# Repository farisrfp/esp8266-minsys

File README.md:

# **ESP8266 Minimum System**

_Workshop Telematika 2023_

## **Deskripsi**

Dokumentasi ini dibuat untuk memudahkan peserta workshop dalam memahami dan mengembangkan ESP8266 Minimum System pada Workshop Telematika 2023.

Diagram Fitur ESP8266 Minimum System dan PCB dapat dilihat pada gambar berikut.

## Hardware

Gambar dibawah merupakan design hardware ESP8266 Minimum System yang akan digunakan pada workshop.

<table>
                <tr>
                    <th>Jalur PCB</th>
                    <th>Hasil Gerber</th>
                    <th>Gambar 3D</th>
                </tr>
                <tr>
                    <td></td>
                    <td></td>
                    <td></td>
                </tr>
</table>

Untuk dokumentasi hardware, silahkan lihat [/hardware](hardware/readme.md)

## Firmware

Untuk dokumentasi firmware, silahkan lihat [/firmware](firmware/readme.md)

## Kontribusi

Kami sangat terbuka terhadap kontribusi dari semua pihak. Jika Anda ingin berkontribusi dengan memperbaiki atau melengkapi template ini, silakan buat pull request ke repositori template kami.

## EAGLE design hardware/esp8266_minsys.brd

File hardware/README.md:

# **Dokumentasi Hardware**

## Software

- [Eagle](https://www.autodesk.com/products/eagle/overview) (Untuk membuka file .sch dan .brd)
- [Fusion 360](https://www.autodesk.com/products/fusion-360/overview) (Alternatif)

## Schematic

Gambar dibawah merupakan schematic ESP8266 Minimum System yang akan digunakan pada workshop.

## Bill of Material

| Designator | Quantity | Package | Value |      Description      |
| :--------: | :------: | :-----: | :---: | :-------------------: |
|  R1 - R4   |    4     |  0805   |  10K  |       Resistor        |
|  R5 - R7   |    3     |  0805   |  330  |       Resistor        |
|  R8 - R10  |    3     |  0805   |  100  |       Resistor        |
|    R11     |    1     |  0805   |  1K   |       Resistor        |
|     C1     |    1     |  2412   | 100u  |       Kapasitor       |
|  C2 - C3   |    2     |  0805   |  10u  |       Kapasitor       |
|     D1     |    1     |  5050   |  RGB  |          LED          |
|     D2     |    1     |  0805   |  Red  |          LED          |
|    SW1     |    1     |    -    |   -   |    Push Button (1)    |
| SW2 - SW3  |    1     |    -    |   -   |    Push Button (2)    |
|    IC1     |    1     | SOT-223 |  3V3  | Voltage Regulator 3V3 |
|     F1     |    1     |  1206   | 750mA |         Fuse          |
|     J1     |    1     |    -    |  6P   |      USB Type-C       |

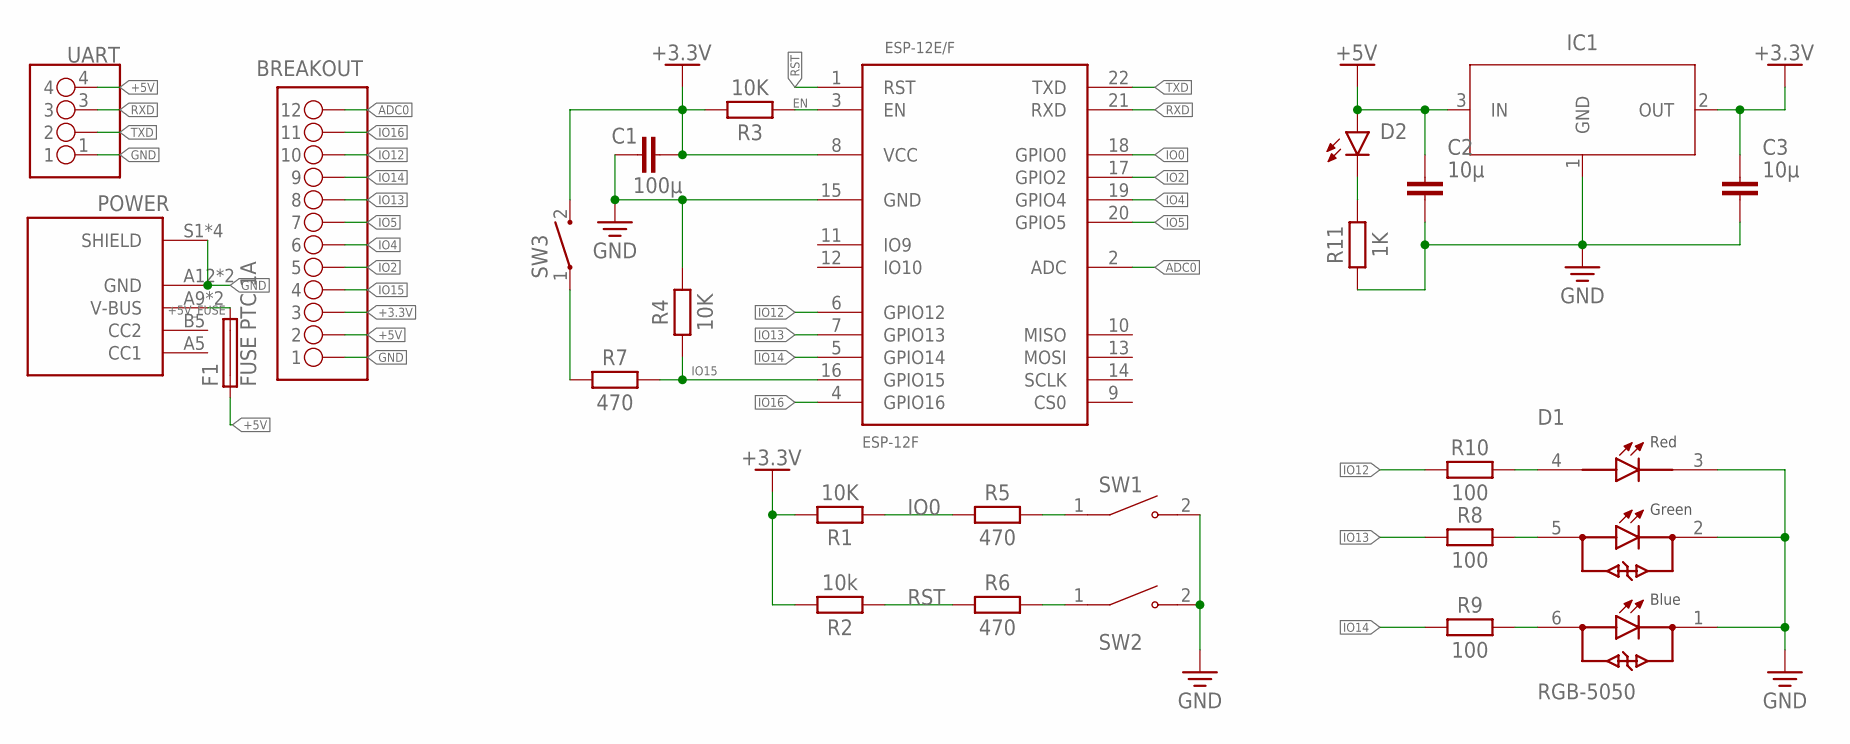
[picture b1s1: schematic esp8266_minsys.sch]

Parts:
BREAKOUT: PINHD-1X12-BACKUP_1X12M; 1X12
C1: 100µ; CAPM6032X280
C2, C3: 10µ; CAPC2012X110
D1: RGB-5050
D2: LED_RED; LEDC2012X110N_FLAT-R
ESP-12E/F: ESP-12F
F1: FUSE PTC 1A; FUSC3215X82N
IC1: NCP1117ST33T3G; SOT230P700X170-4
POWER: SOCKET-C
R1, R3, R4: 10K; RESC2012X65
R2: 10k; RESC2012X65
R5, R6, R7: 470; RESC2012X65
R8, R9, R10: 100; RESC2012X65
R11: 1K; RESC2012X65
SW1, SW2: SWITCH-2P
SW3: SWITCH; SW_1437566-3
UART: PINHD-1X04_1X04M; 1X04

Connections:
+3.3V: BREAKOUT.3, C1.2, C3.1, ESP-12E/F.8 (VCC), IC1.2 (OUT), R1.2, R2.2, R3.2, SW3.2
+5V: BREAKOUT.2, C2.1, D2.A, F1.1, IC1.3 (IN), UART.4
+5V_FUSE: F1.2, POWER.A9 (V-BUS), POWER.B9 (V-BUS)
ADC0: BREAKOUT.12, ESP-12E/F.2 (ADC)
EN: ESP-12E/F.3 (EN), R3.1
GND: BREAKOUT.1, C1.1, C2.2, C3.2, D1.1, D1.2, D1.3, ESP-12E/F.15 (GND), IC1.1 (GND), POWER.A12 (GND), POWER.B12 (GND), POWER.S1 (SHIELD), POWER.S2 (SHIELD), POWER.S3 (SHIELD), POWER.S4 (SHIELD), R4.2, R11.1, SW1.2, SW2.2, UART.1
IO0: ESP-12E/F.18 (GPIO0), R1.1, R5.1
IO2: BREAKOUT.5, ESP-12E/F.17 (GPIO2)
IO4: BREAKOUT.6, ESP-12E/F.19 (GPIO4)
IO5: BREAKOUT.7, ESP-12E/F.20 (GPIO5)
IO12: BREAKOUT.10, ESP-12E/F.6 (GPIO12), R10.1
IO13: BREAKOUT.8, ESP-12E/F.7 (GPIO13), R8.1
IO14: BREAKOUT.9, ESP-12E/F.5 (GPIO14), R9.1
IO15: BREAKOUT.4, ESP-12E/F.16 (GPIO15), R4.1, R7.2
IO16: BREAKOUT.11, ESP-12E/F.4 (GPIO16)
unnamed: D1.4, R10.2
unnamed: D1.5, R8.2
unnamed: D1.6, R9.2
unnamed: R5.2, SW1.1
unnamed: R6.2, SW2.1
unnamed: R7.1, SW3.1
unnamed: D2.C, R11.2
RST: ESP-12E/F.1 (RST), R2.1, R6.1
RXD: ESP-12E/F.21 (RXD), UART.3
TXD: ESP-12E/F.22 (TXD), UART.2

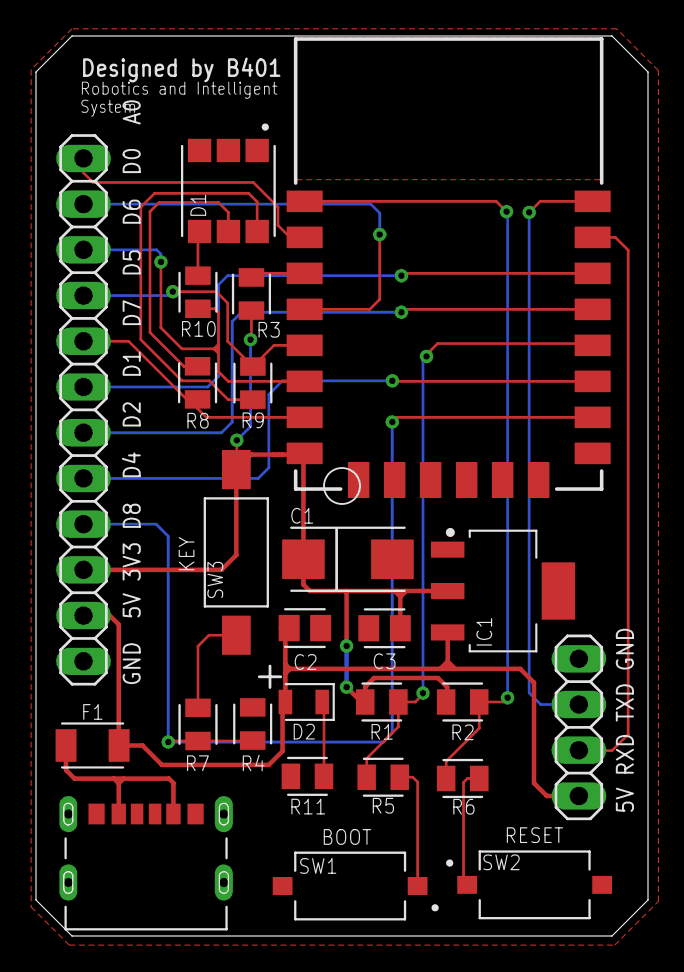
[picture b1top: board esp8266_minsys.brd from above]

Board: 2 copper layers, 34.0 x 50.0 mm, 25 parts (0 on the bottom side), 25 nets.

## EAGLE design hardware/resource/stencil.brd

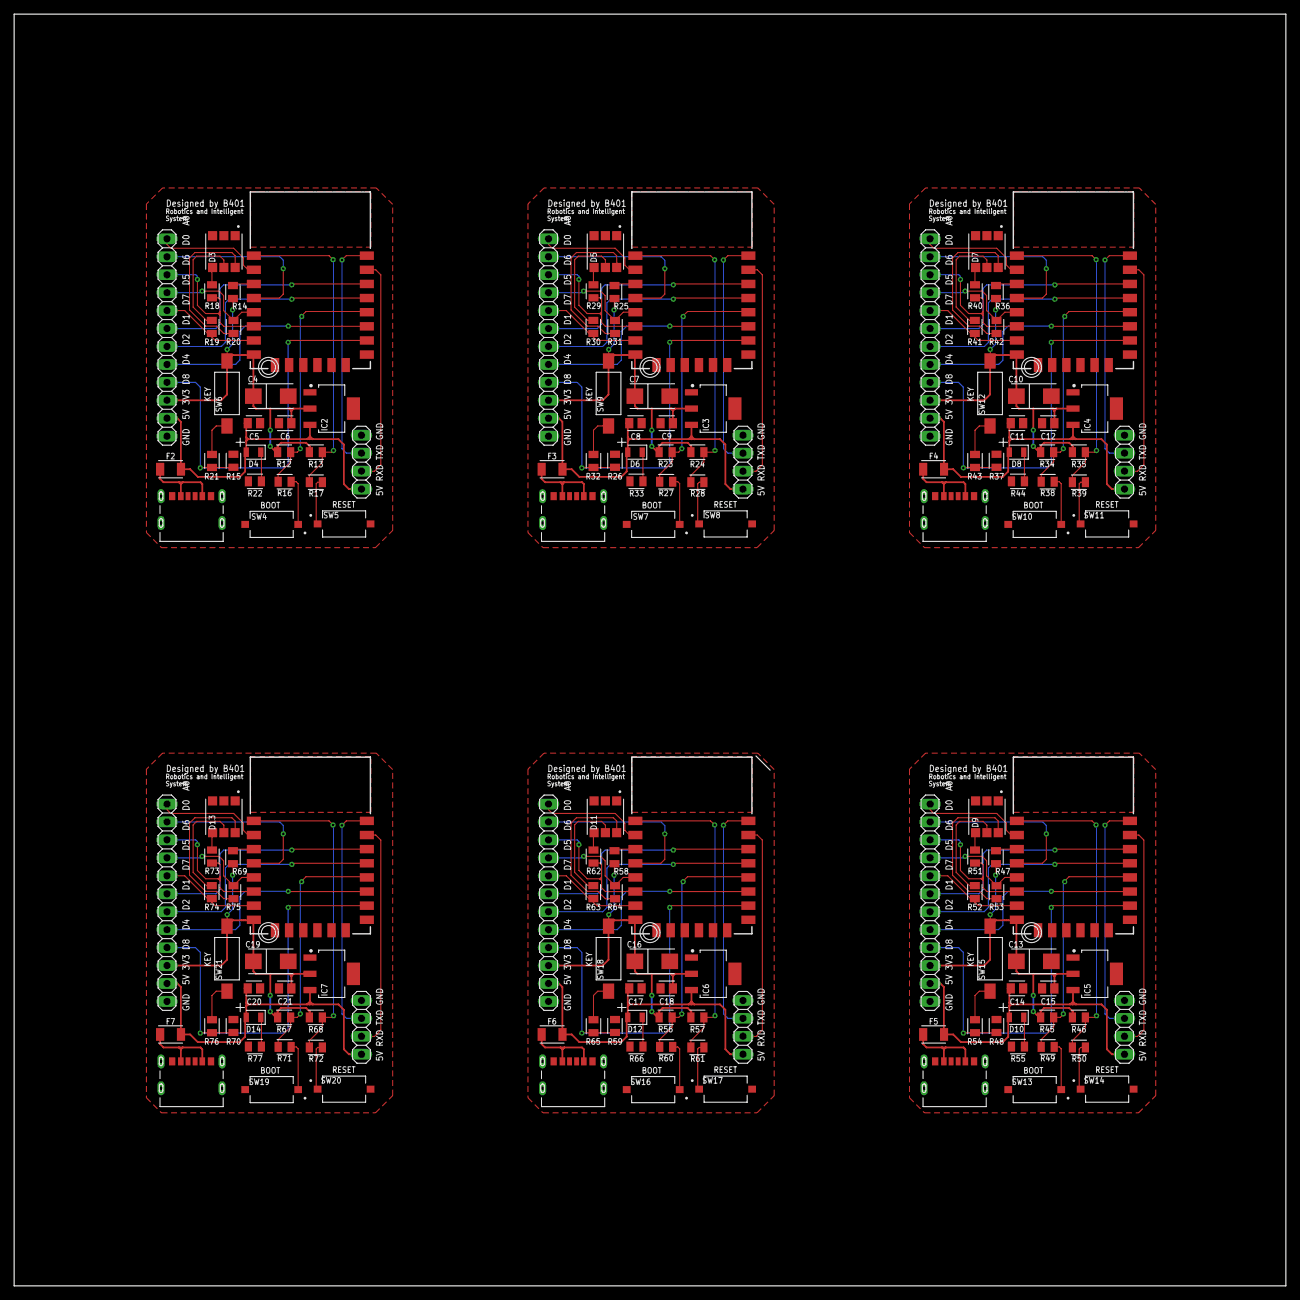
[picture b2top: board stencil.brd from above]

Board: 2 copper layers, 180.0 x 180.0 mm, 150 parts (0 on the bottom side), 150 nets.

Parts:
BREAKOUT1, BREAKOUT2, BREAKOUT3, BREAKOUT4, BREAKOUT5, BREAKOUT6: PINHD-1X12-BACKUP_1X12M; 1X12
C4, C7, C10, C13, C16, C19: 100µ; CAPM6032X280
C5, C6, C8, C9, C11, C12, C14, C15, C17, C18, C20, C21: 10µ; CAPC2012X110
D3, D5, D7, D9, D11, D13: RGB-5050
D4, D6, D8, D10, D12, D14: LED_RED; LEDC2012X110N_FLAT-R
ESP-12E/F1, ESP-12E/F2, ESP-12E/F3, ESP-12E/F4, ESP-12E/F5, ESP-12E/F6: ESP-12F
F2, F3, F4, F5, F6, F7: FUSE PTC 1A; FUSC3215X82N
IC2, IC3, IC4, IC5, IC6, IC7: NCP1117ST33T3G; SOT230P700X170-4
POWER1, POWER2, POWER3, POWER4, POWER5, POWER6: SOCKET-C
R12, R14, R15, R23, R25, R26, R34, R36, R37, R45, R47, R48, R56, R58, R59, R67, R69, R70: 10K; RESC2012X65
R13, R24, R35, R46, R57, R68: 10k; RESC2012X65
R16, R17, R21, R27, R28, R32, R38, R39, R43, R49, R50, R54, R60, R61, R65, R71, R72, R76: 470; RESC2012X65
R18, R19, R20, R22, R29, R30, R31, R33, R40, R41, R42, R44, R51, R52, R53, R55, R62, R63, R64, R66, R73, R74, R75, R77: 100; RESC2012X65
SW4, SW5, SW7, SW8, SW10, SW11, SW13, SW14, SW16, SW17, SW19, SW20: SWITCH-2P
SW6, SW9, SW12, SW15, SW18, SW21: SWITCH; SW_1437566-3
UART1, UART2, UART3, UART4, UART5, UART6: PINHD-1X04_1X04M; 1X04

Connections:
+3.3V1: BREAKOUT1.3, C4.2, C6.1, ESP-12E/F1.8, IC2.2, R12.2, R13.2, R14.2, SW6.2
+3.3V2: BREAKOUT2.3, C7.2, C9.1, ESP-12E/F2.8, IC3.2, R23.2, R24.2, R25.2, SW9.2
+3.3V3: BREAKOUT3.3, C10.2, C12.1, ESP-12E/F3.8, IC4.2, R34.2, R35.2, R36.2, SW12.2
+3.3V4: BREAKOUT4.3, C13.2, C15.1, ESP-12E/F4.8, IC5.2, R45.2, R46.2, R47.2, SW15.2
+3.3V5: BREAKOUT5.3, C16.2, C18.1, ESP-12E/F5.8, IC6.2, R56.2, R57.2, R58.2, SW18.2
+3.3V6: BREAKOUT6.3, C19.2, C21.1, ESP-12E/F6.8, IC7.2, R67.2, R68.2, R69.2, SW21.2
+5V1: BREAKOUT1.2, C5.1, D4.A, F2.1, IC2.3, UART1.4
+5V2: BREAKOUT2.2, C8.1, D6.A, F3.1, IC3.3, UART2.4
+5V3: BREAKOUT3.2, C11.1, D8.A, F4.1, IC4.3, UART3.4
+5V4: BREAKOUT4.2, C14.1, D10.A, F5.1, IC5.3, UART4.4
+5V5: BREAKOUT5.2, C17.1, D12.A, F6.1, IC6.3, UART5.4
+5V6: BREAKOUT6.2, C20.1, D14.A, F7.1, IC7.3, UART6.4
+5V_FUSE1: F2.2, POWER1.A9, POWER1.B9
+5V_FUSE2: F3.2, POWER2.A9, POWER2.B9
+5V_FUSE3: F4.2, POWER3.A9, POWER3.B9
+5V_FUSE4: F5.2, POWER4.A9, POWER4.B9
+5V_FUSE5: F6.2, POWER5.A9, POWER5.B9
+5V_FUSE6: F7.2, POWER6.A9, POWER6.B9
ADC1: BREAKOUT1.12, ESP-12E/F1.2
ADC2: BREAKOUT2.12, ESP-12E/F2.2
ADC3: BREAKOUT3.12, ESP-12E/F3.2
ADC4: BREAKOUT4.12, ESP-12E/F4.2
ADC5: BREAKOUT5.12, ESP-12E/F5.2
ADC6: BREAKOUT6.12, ESP-12E/F6.2
EN1: ESP-12E/F1.3, R14.1
EN2: ESP-12E/F2.3, R25.1
EN3: ESP-12E/F3.3, R36.1
EN4: ESP-12E/F4.3, R47.1
EN5: ESP-12E/F5.3, R58.1
EN6: ESP-12E/F6.3, R69.1
GND1: BREAKOUT1.1, C4.1, C5.2, C6.2, D3.1, D3.2, D3.3, ESP-12E/F1.15, IC2.1, POWER1.A12, POWER1.B12, POWER1.S1, POWER1.S2, POWER1.S3, POWER1.S4, R15.2, R22.1, SW4.2, SW5.2, UART1.1
GND2: BREAKOUT2.1, C7.1, C8.2, C9.2, D5.1, D5.2, D5.3, ESP-12E/F2.15, IC3.1, POWER2.A12, POWER2.B12, POWER2.S1, POWER2.S2, POWER2.S3, POWER2.S4, R26.2, R33.1, SW7.2, SW8.2, UART2.1
GND3: BREAKOUT3.1, C10.1, C11.2, C12.2, D7.1, D7.2, D7.3, ESP-12E/F3.15, IC4.1, POWER3.A12, POWER3.B12, POWER3.S1, POWER3.S2, POWER3.S3, POWER3.S4, R37.2, R44.1, SW10.2, SW11.2, UART3.1
GND4: BREAKOUT4.1, C13.1, C14.2, C15.2, D9.1, D9.2, D9.3, ESP-12E/F4.15, IC5.1, POWER4.A12, POWER4.B12, POWER4.S1, POWER4.S2, POWER4.S3, POWER4.S4, R48.2, R55.1, SW13.2, SW14.2, UART4.1
GND5: BREAKOUT5.1, C16.1, C17.2, C18.2, D11.1, D11.2, D11.3, ESP-12E/F5.15, IC6.1, POWER5.A12, POWER5.B12, POWER5.S1, POWER5.S2, POWER5.S3, POWER5.S4, R59.2, R66.1, SW16.2, SW17.2, UART5.1
GND6: BREAKOUT6.1, C19.1, C20.2, C21.2, D13.1, D13.2, D13.3, ESP-12E/F6.15, IC7.1, POWER6.A12, POWER6.B12, POWER6.S1, POWER6.S2, POWER6.S3, POWER6.S4, R70.2, R77.1, SW19.2, SW20.2, UART6.1
IO1: ESP-12E/F1.18, R12.1, R16.1
IO3: BREAKOUT1.10, ESP-12E/F1.6, R18.1
IO6: BREAKOUT1.8, ESP-12E/F1.7, R19.1
IO7: BREAKOUT1.9, ESP-12E/F1.5, R20.1
IO8: BREAKOUT1.6, ESP-12E/F1.19
IO9: BREAKOUT1.7, ESP-12E/F1.20
IO10: BREAKOUT1.11, ESP-12E/F1.4
IO11: BREAKOUT1.5, ESP-12E/F1.17
IO17: BREAKOUT1.4, ESP-12E/F1.16, R15.1, R21.2
IO18: ESP-12E/F2.18, R23.1, R27.1
IO19: BREAKOUT2.10, ESP-12E/F2.6, R29.1
IO20: BREAKOUT2.8, ESP-12E/F2.7, R30.1
IO21: BREAKOUT2.9, ESP-12E/F2.5, R31.1
IO22: BREAKOUT2.6, ESP-12E/F2.19
IO23: BREAKOUT2.7, ESP-12E/F2.20
IO24: BREAKOUT2.11, ESP-12E/F2.4
IO25: BREAKOUT2.5, ESP-12E/F2.17
IO26: BREAKOUT2.4, ESP-12E/F2.16, R26.1, R32.2
IO27: ESP-12E/F3.18, R34.1, R38.1
IO28: BREAKOUT3.10, ESP-12E/F3.6, R40.1
IO29: BREAKOUT3.8, ESP-12E/F3.7, R41.1
IO30: BREAKOUT3.9, ESP-12E/F3.5, R42.1
IO31: BREAKOUT3.6, ESP-12E/F3.19
IO32: BREAKOUT3.7, ESP-12E/F3.20
IO33: BREAKOUT3.11, ESP-12E/F3.4
IO34: BREAKOUT3.5, ESP-12E/F3.17
IO35: BREAKOUT3.4, ESP-12E/F3.16, R37.1, R43.2
IO36: ESP-12E/F4.18, R45.1, R49.1
IO37: BREAKOUT4.10, ESP-12E/F4.6, R51.1
IO38: BREAKOUT4.8, ESP-12E/F4.7, R52.1
IO39: BREAKOUT4.9, ESP-12E/F4.5, R53.1
IO40: BREAKOUT4.6, ESP-12E/F4.19
IO41: BREAKOUT4.7, ESP-12E/F4.20
IO42: BREAKOUT4.11, ESP-12E/F4.4
IO43: BREAKOUT4.5, ESP-12E/F4.17
IO44: BREAKOUT4.4, ESP-12E/F4.16, R48.1, R54.2
IO45: ESP-12E/F5.18, R56.1, R60.1
IO46: BREAKOUT5.10, ESP-12E/F5.6, R62.1
IO47: BREAKOUT5.8, ESP-12E/F5.7, R63.1
IO48: BREAKOUT5.9, ESP-12E/F5.5, R64.1
IO49: BREAKOUT5.6, ESP-12E/F5.19
IO50: BREAKOUT5.7, ESP-12E/F5.20
IO51: BREAKOUT5.11, ESP-12E/F5.4
IO52: BREAKOUT5.5, ESP-12E/F5.17
IO53: BREAKOUT5.4, ESP-12E/F5.16, R59.1, R65.2
IO54: ESP-12E/F6.18, R67.1, R71.1
IO55: BREAKOUT6.10, ESP-12E/F6.6, R73.1
IO56: BREAKOUT6.8, ESP-12E/F6.7, R74.1
IO57: BREAKOUT6.9, ESP-12E/F6.5, R75.1
IO58: BREAKOUT6.6, ESP-12E/F6.19
IO59: BREAKOUT6.7, ESP-12E/F6.20
IO60: BREAKOUT6.11, ESP-12E/F6.4
IO61: BREAKOUT6.5, ESP-12E/F6.17
IO62: BREAKOUT6.4, ESP-12E/F6.16, R70.1, R76.2
unnamed: R16.2, SW4.1
unnamed: R17.2, SW5.1
unnamed: D3.4, R18.2
unnamed: D3.5, R19.2
unnamed: D3.6, R20.2
unnamed: R21.1, SW6.1
unnamed: D4.C, R22.2
unnamed: R27.2, SW7.1
unnamed: R28.2, SW8.1
unnamed: D5.4, R29.2
unnamed: D5.5, R30.2
unnamed: D5.6, R31.2
unnamed: R32.1, SW9.1
unnamed: D6.C, R33.2
unnamed: R38.2, SW10.1
unnamed: R39.2, SW11.1
unnamed: D7.4, R40.2
unnamed: D7.5, R41.2
unnamed: D7.6, R42.2
unnamed: R43.1, SW12.1
unnamed: D8.C, R44.2
unnamed: R49.2, SW13.1
unnamed: R50.2, SW14.1
unnamed: D9.4, R51.2
unnamed: D9.5, R52.2
unnamed: D9.6, R53.2
unnamed: R54.1, SW15.1
unnamed: D10.C, R55.2
unnamed: R60.2, SW16.1
unnamed: R61.2, SW17.1
unnamed: D11.4, R62.2
unnamed: D11.5, R63.2
unnamed: D11.6, R64.2
unnamed: R65.1, SW18.1
unnamed: D12.C, R66.2
unnamed: R71.2, SW19.1
unnamed: R72.2, SW20.1
unnamed: D13.4, R73.2
unnamed: D13.5, R74.2
unnamed: D13.6, R75.2
unnamed: R76.1, SW21.1
unnamed: D14.C, R77.2
RST1: ESP-12E/F1.1, R13.1, R17.1
RST2: ESP-12E/F2.1, R24.1, R28.1
RST3: ESP-12E/F3.1, R35.1, R39.1
RST4: ESP-12E/F4.1, R46.1, R50.1
RST5: ESP-12E/F5.1, R57.1, R61.1
RST6: ESP-12E/F6.1, R68.1, R72.1
RXD1: ESP-12E/F1.21, UART1.3
RXD2: ESP-12E/F2.21, UART2.3
RXD3: ESP-12E/F3.21, UART3.3
RXD4: ESP-12E/F4.21, UART4.3
RXD5: ESP-12E/F5.21, UART5.3
RXD6: ESP-12E/F6.21, UART6.3
TXD1: ESP-12E/F1.22, UART1.2
TXD2: ESP-12E/F2.22, UART2.2
TXD3: ESP-12E/F3.22, UART3.2
TXD4: ESP-12E/F4.22, UART4.2
TXD5: ESP-12E/F5.22, UART5.2
TXD6: ESP-12E/F6.22, UART6.2

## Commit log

2023-11-05 init upload
2023-11-05 add README.md
2023-11-05 add LICENSE
2023-11-10 feat: images and hardware doc
